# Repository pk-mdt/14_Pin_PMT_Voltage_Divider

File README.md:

# 14_Pin_PMT_Voltage_Divider
 14 Pin Voltage Divider for Saint Gobain PMT

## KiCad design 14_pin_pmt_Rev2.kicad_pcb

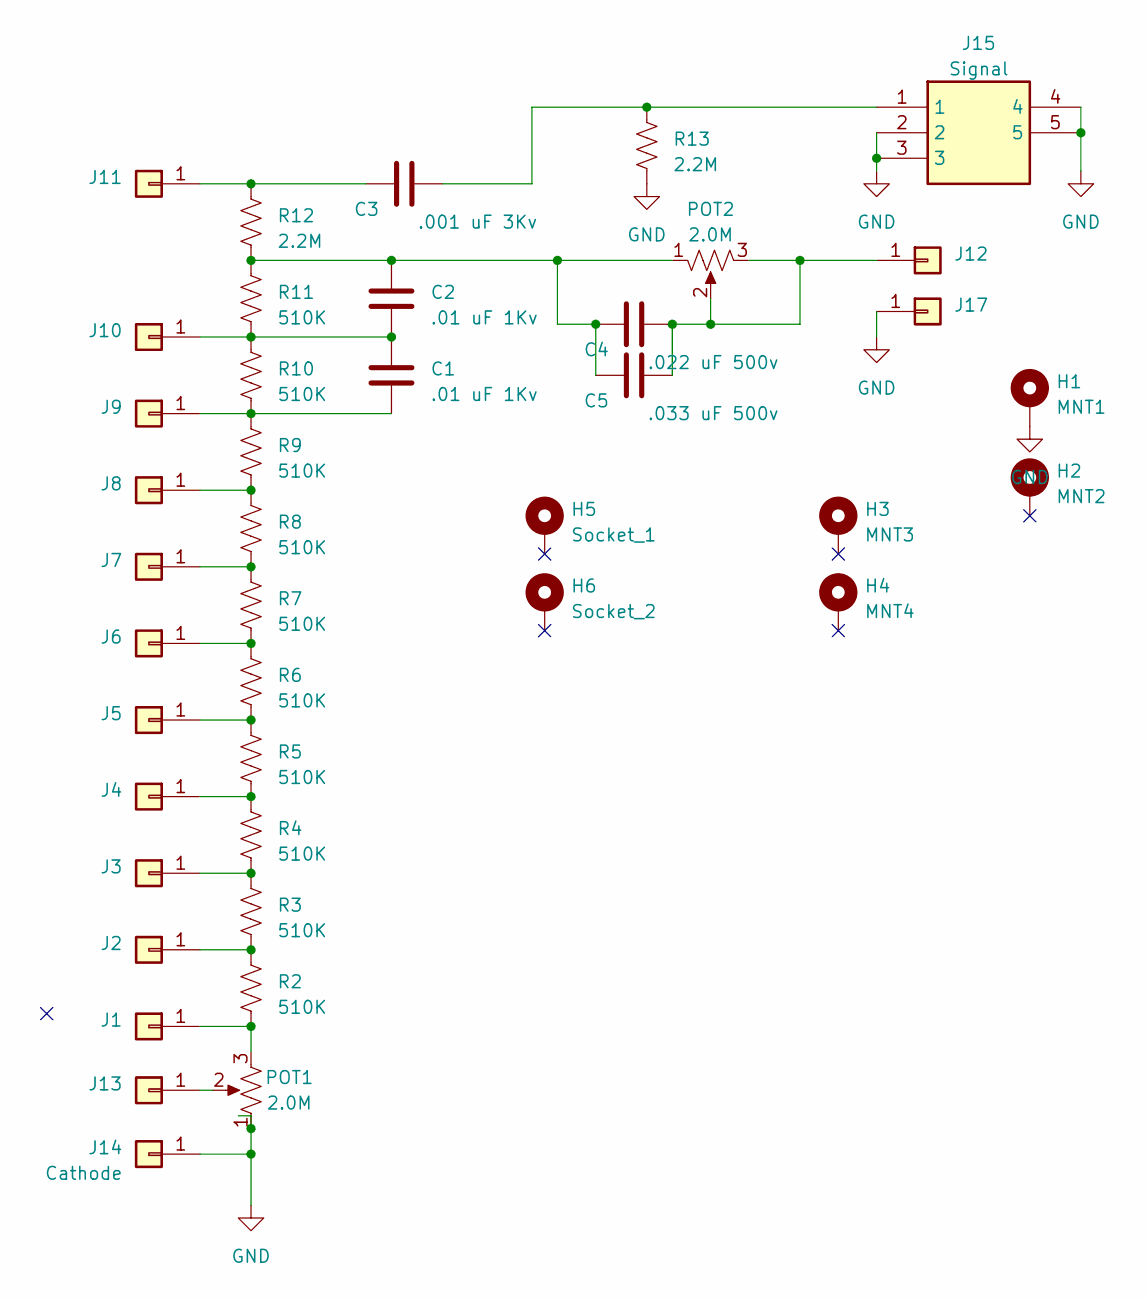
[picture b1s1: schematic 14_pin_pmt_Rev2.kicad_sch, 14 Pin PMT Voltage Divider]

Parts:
C1, C2: .01 uF 1Kv; C_1206_3216Metric; Manufacturer_Part_Number 1206B103M102CT
C3: .001 uF 3Kv; C_1812_4532Metric; Manufacturer_Part_Number C1812C102KHRACTU
C4: .022 uF 500v; C_1206_3216Metric; Manufacturer_Part_Number CL31B223KHHNNNE
C5: .033 uF 500v; C_1206_3216Metric; Manufacturer_Part_Number CL31B333KHHSFNE
H1: MNT1; MountingHole_2.2mm_M2_Pad_Via
H2: MNT2; MountingHole_2.2mm_M2_Pad_Via
H3: MNT3; MountingHole_2.2mm_M2_Pad_Via
H4: MNT4; MountingHole_2.2mm_M2_Pad_Via
H5: Socket_1; MountingHole_3mm_Pad_Via
H6: Socket_2; MountingHole_3mm_Pad_Via
J1: Dynode 1; SolderWire-1.5sqmm_1x01_D1.7mm_OD3.9mm
J2: Dynode 2; SolderWire-1.5sqmm_1x01_D1.7mm_OD3.9mm
J3: Dynode 3; SolderWire-1.5sqmm_1x01_D1.7mm_OD3.9mm
J4: Dynode 4; SolderWire-1.5sqmm_1x01_D1.7mm_OD3.9mm
J5: Dynode 5; SolderWire-1.5sqmm_1x01_D1.7mm_OD3.9mm
J6: Dynode 6; SolderWire-1.5sqmm_1x01_D1.7mm_OD3.9mm
J7: Dynode 7; SolderWire-1.5sqmm_1x01_D1.7mm_OD3.9mm
J8: Dynode 8; SolderWire-1.5sqmm_1x01_D1.7mm_OD3.9mm
J9: Dynode 9; SolderWire-1.5sqmm_1x01_D1.7mm_OD3.9mm
J10: Dynode 10; SolderWire-1.5sqmm_1x01_D1.7mm_OD3.9mm
J11: Anode; SolderWire-1.5sqmm_1x01_D1.7mm_OD3.9mm
J12: Pin1; SolderWire-1.5sqmm_1x01_D1.7mm_OD3.9mm
J13: Focus; SolderWire-1.5sqmm_1x01_D1.7mm_OD3.9mm
J14: Cathode; SolderWire-1.5sqmm_1x01_D1.7mm_OD3.9mm
J15: Signal; SMACONNECTOR_LPRS; Mouser Part Number 471-SMACONNECTOR
J17: GND; SolderWire-1.5sqmm_1x01_D1.7mm_OD3.9mm
POT1, POT2: 2.0M; TRIM_3006P-1-202; Manufacturer_Part_Number 3006P-1-205LF
R2, R3, R4, R5, R6, R7, R8, R9, R10, R11: 510K; R_0805_2012Metric; Manufacturer_Part_Number ERJ-P06F5103V
R12, R13: 2.2M; R_2512_6332Metric; Manufacturer_Part_Number CHV2512-FX-2204ELF

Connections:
GND: H1.1, J14.1, J15.2, J15.3, J15.4, J15.5, J17.1, POT1.1, R13.2; also elsewhere on the board
unnamed: C2.1, C4.2, C5.2, POT2.1, R11.1, R12.2
unnamed 2: C3.1, J15.1, R13.1; also elsewhere on the board
unnamed: J1.1, POT1.3, R2.2
unnamed: J2.1, R2.1, R3.2
unnamed: J3.1, R3.1, R4.2
unnamed: J4.1, R4.1, R5.2
unnamed: J5.1, R5.1, R6.2
unnamed: J6.1, R6.1, R7.2
unnamed: J7.1, R7.1, R8.2
unnamed: J8.1, R8.1, R9.2
unnamed: C1.2, J9.1, R9.1, R10.2
unnamed: C1.1, C2.2, J10.1, R10.1, R11.2
unnamed: C3.2, J11.1, R12.1
unnamed: C4.1, C5.1, J12.1, POT2.2, POT2.3
unnamed: J13.1, POT1.2

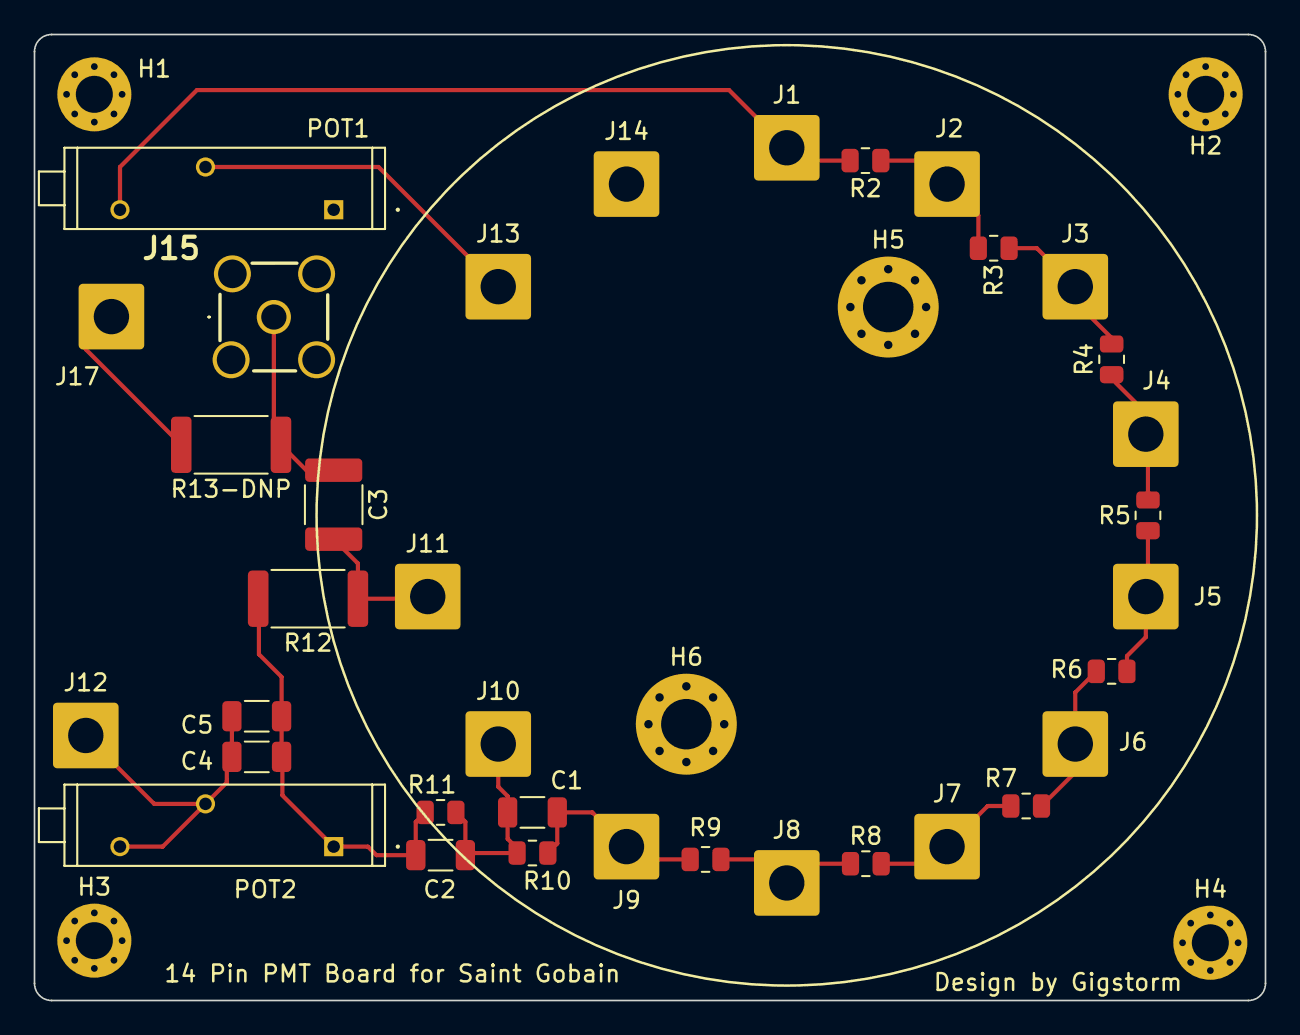
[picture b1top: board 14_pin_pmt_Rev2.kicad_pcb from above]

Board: 2 copper layers, 73.2 x 57.4 mm, 41 parts (0 on the bottom side), 16 nets.

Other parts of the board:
R13-DNP: 2.2M; R_2512_6332Metric

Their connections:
GND: R13-DNP.2; also elsewhere on the board
unnamed 2: R13-DNP.1; also elsewhere on the board

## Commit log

2023-08-04 added title blocks
